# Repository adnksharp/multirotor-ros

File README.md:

# Multirotor-ROS

|  |
|---|

Plataforma de adquisición de datos de un multirotor con ESP32 y ROS2

## Software y Hardware 

<details>
    <summary>Software</summary>

* [ROS2 Jazzy](https://index.ros.org/p/desktop_full/#jazzy)
* [Gazebo Harmonic](https://gazebosim.org/docs/harmonic/getstarted/)
* [uROS Jazzy](https://github.com/micro-ROS/micro_ros_setup/tree/jazzy)
* [uROS Arduino Jazzy](https://github.com/micro-ROS/micro_ros_arduino/tree/jazzy)
* [KiCad](https://www.kicad.org)

</details>

<details>
    <summary>Componentes electrónicos</summary>

* 1 [ESP-WROOM-32 Devkit](https://www.amazon.com/-/es/ESP32-DevKitC-ESP32-WROOM-32-ESP32-WROVER/dp/B07W6F2Z3K)
* 1 Módulo IMU [MPU6050](https://www.amazon.com/-/es/MPU6050-Accelerometer-Gyroscope-Module-Arduino/dp/B00KQK8X2A)
* 1 Módulo GPS [NEO-6M](https://www.amazon.com/-/es/NEO-6M-GPS-Module-For-Arduino/dp/B00KQK8X2A)
* 1 Sensor de temp. y humedad [DHT22](https://www.amazon.com/-/es/DHT11-Temperature-Humidity-Sensor-Arduino/dp/B00KQK8X2A)
* 1 Resistencia de 10KΩ
* 1 Módulo [BMP280](https://www.amazon.com/-/es/BME280-Temperature-Humidity-Barometric-Pressure/dp/B00KQK8X2A)
* 4 Módulos sensores de distancia [HC-SR04](https://www.amazon.com/-/es/HC-SR04-Ultrasonic-Distance-Transducer-Arduino/dp/B00KQK8X2A)
* 1 Pantalla [OLED 0.96"](https://www.amazon.com/-/es/0-96-Inch-OLED-Display-Arduino/dp/B00KQK8X2A)
* 4 Motores brushless [1000KV](https://www.amazon.com/-/es/Brushless-Motor-1000KV-Drone-Quadcopter/dp/B00KQK8X2A)
* 4 Controladores de velocidad [(ESC) 30A](https://www.amazon.com/-/es/Brushless-Controller-30A-Quadcopter-Multicopter/dp/B00KQK8X2A)
* 1 Batería LiPo [2S 4Ah](https://www.amazon.com/-/es/LiPo-Battery-2200mAh-3S-11-1V/dp/B00KQK8X2A)
* 1 Powerbank [30A 3.7V](https://www.amazon.com/-/es/Power-Bank-3-7V-30A/dp/B00KQK8X2A)

</details>

<details>
    <summary>Componentes mecánicos</summary>

* 1 Chasis de multirotor [F450](https://www.amazon.com/-/es/F450-Quadcopter-Frame-Kit-Quadcopter/dp/B00KQK8X2A)
* 4 Hélices [1045](https://www.amazon.com/-/es/1045-Propeller-Quadcopter-Multicopter-Drone/dp/B00KQK8X2A)
* Piezas impresas en 3D

</details>

## Instalación
Es posible instalar el software de [ROS2](https://docs.ros.org/en/jazzy/index.html), [Gazebo](https://gazebosim.org/docs/harmonic/install/) y [micro-ROS](https://micro.ros.org/docs/tutorials/core/overview/) siguiendo los pasos de la documentación oficial o con el script de instalación [install-ros.sh](./src/install-ros.sh):

```shell
$SHELL ./src/install-ros.sh
```

## Espacio de trabajo (ROS2)
[ros-ws](ros-ws) es el espacio de trabajo de ROS2 donde se compila el paquete `fdrone` usando para visualizar y simular el multirotor en Gazebo.

```shell
cd ros-ws
colcon build
```

### Lanzador
El lanzador `display.launch.py` se encarga de visualizar el modelo en RVIZ y Gazebo.

```shell
source install/setup.$(echo $SHELL | awk -F '/' '{print $NF}')
ros2 launch fdrone display.launch.py
```

### Interfaz de usuario
El script `vel_put.py` se desarrolló para enviar velocidades al multirotor desde la terminal enviando valores de tipo `Float64` a tópicos puenteados entre ROS2 y Gazebo.

```shell
source install/setup.$(echo $SHELL | awk -F '/' '{print $NF}')
ros2 run fdrone vel_put.py
```

## Electrónica
[electronic](electronic) contiene el esquema eléctrico de la PCB principal.

|  |  |
|---|---|

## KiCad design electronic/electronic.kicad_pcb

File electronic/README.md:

# Esquema electrónico principal

El proyecto se desarrolló usando [KiCAD](https://www.kicad.org/). [electronic.kicad_pro](electronic.kicad_pro) se desarrollo para comunicar multiples sensores a una placa de ESP32. Los componentes utilizados para esta PCB son:

* 1 **ESP32 WROOM-32** DevKit
* 1 Módulo **MPU6050**
* 1 Módulo **BMP280**
* 1 Módulo **NEO6M GPS**
* 1 Pantalla **OLED 128x64**
* 1 Sensor **DHT22**
* 1 Resistencia de 10K $\Omega$
* 4 Módulos **HC-SR04**
* 1 Conector **B2B-XH-A** para la batería
* 1 Conector **B4B-XH-A** para los motores
* **PinSockets** de 2.54mm

## Esquema

El esquema electrónico se encuentra dividido en 8 partes:

* 5 partes indican los componentes que contienen los módulos **MPU6050**, **BMP280**, **NEO6M GPS**, **OLED 128x64** y **DHT22** y etiquetas de los pines de conexión.
* 1 parte indica la conexión de los módulos **HC-SR04** y etiquetas para los pines de conexión de cada módulo.
* 1 parte indica la conexión de los pines de control de los motores y la lectura del estado de la batería.
* La última parte indica la conexión del ESP32 con los componentes mencionados anteriormente.

## PCB

El diseño de la PCB contiene terminales de tipo PinSocket de 2.54mm para la conexión de los módulos **BMP280**, **NEO6M GPS**, **OLED 128x64**, **HC-SR04** y el **ESP32 WROOM-32**. También contiene un conector de tipo **B2B-XH-A** para la lectura de la batería y un conector de tipo **B4B-XH-A** para el control de los motores. Por último, el diseño de la PCB incluye el módulo **MPU6050**, el sensor **DHT22** y la resistencia de 10K $\Omega$.

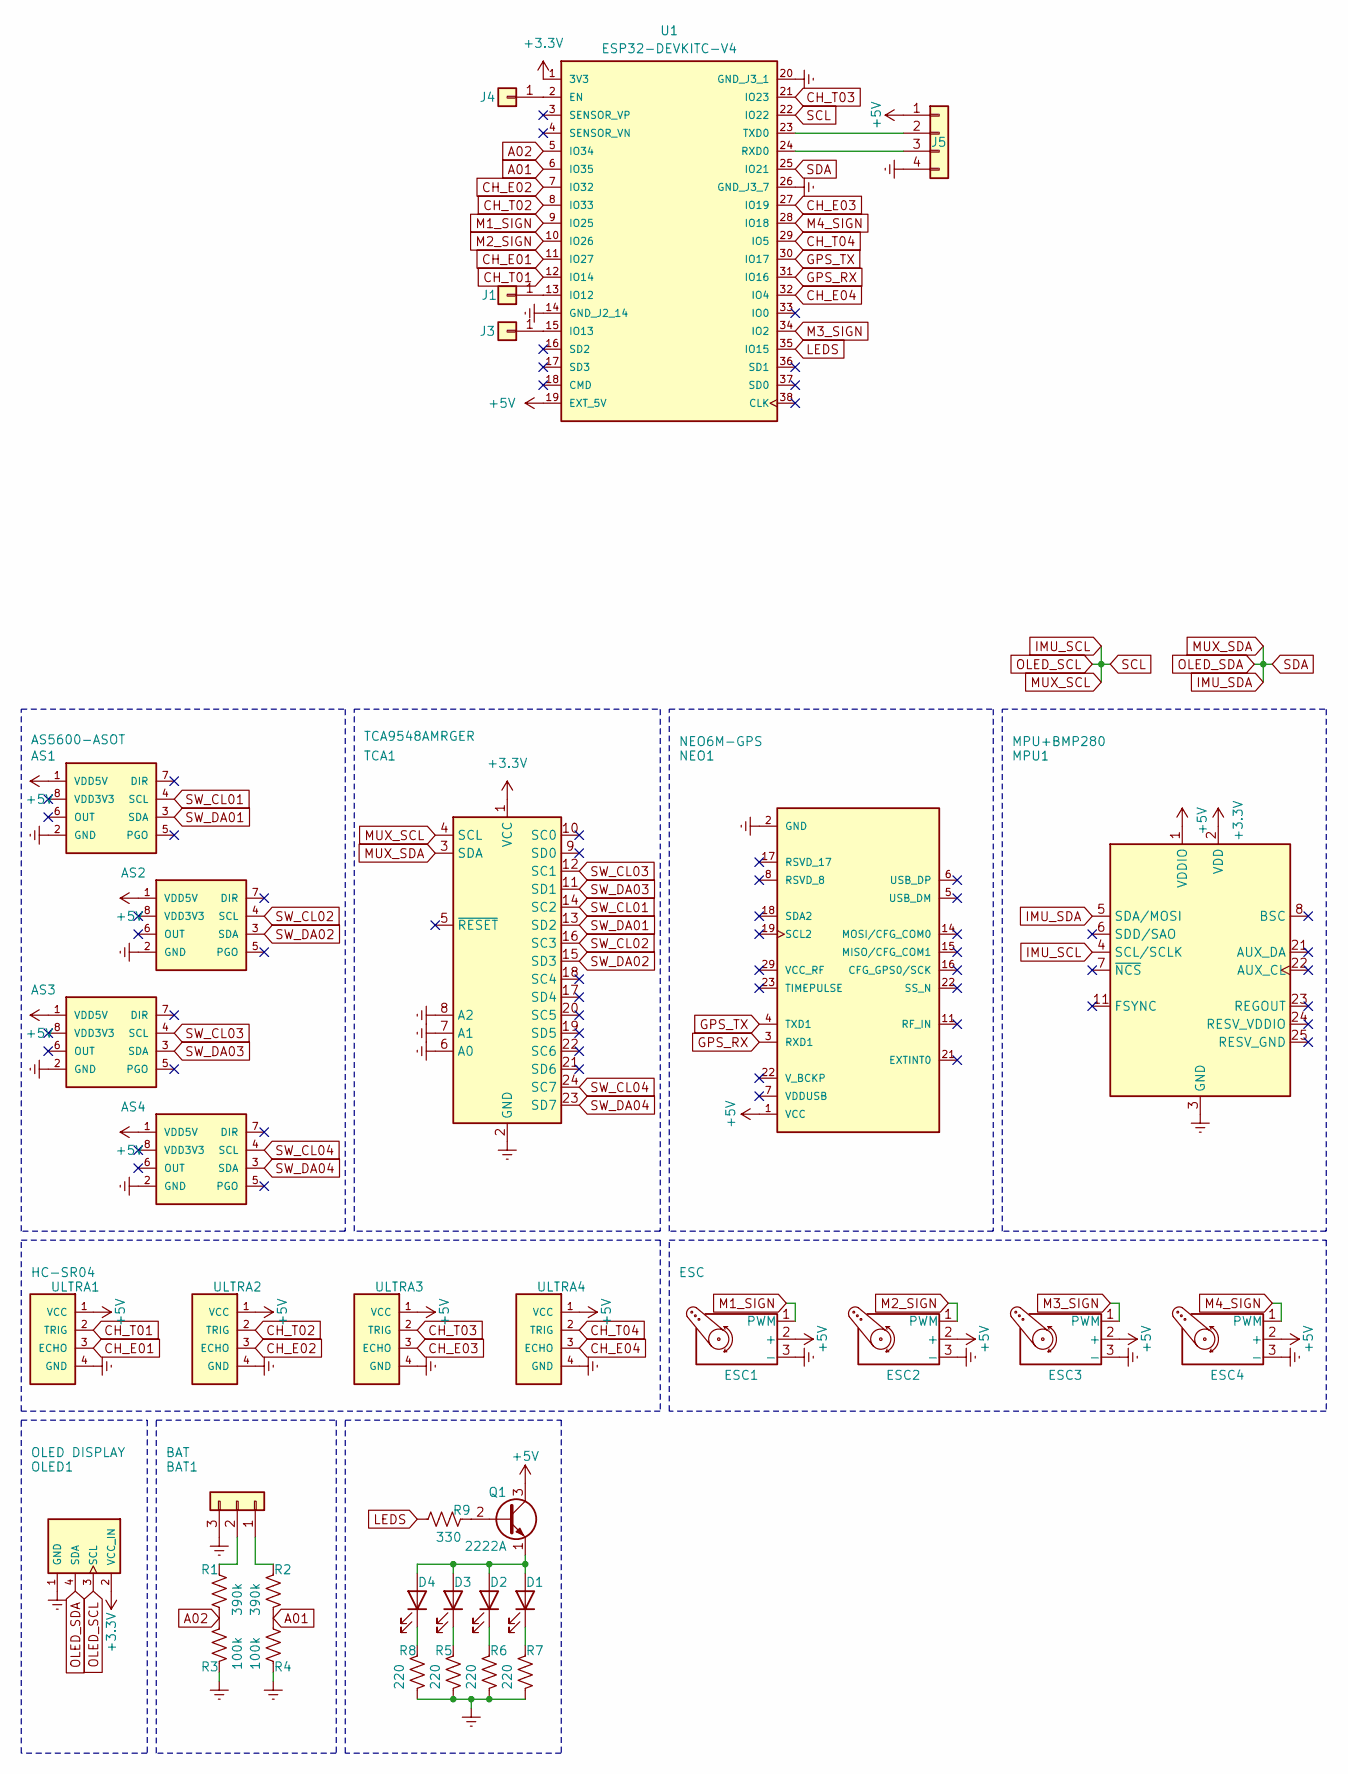
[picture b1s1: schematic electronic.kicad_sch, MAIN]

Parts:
AS1, AS2, AS3, AS4: AS5600-ASOT; PinSocket_1x04_P2.54mm_Horizontal; MOUSER_PART_NUMBER 985-AS5600-ASOT
BAT1: BAT; JST_XH_B3B-XH-A_1x03_P2.50mm_Vertical
D1, D2, D3, D4: LED; PinHeader_1x02_P2.54mm_Vertical
ESC1: ESC; ESC1
ESC2: ESC; ESC2
ESC3: ESC; ESC3
ESC4: ESC; ESC4
J1, J3, J4: Conn_01x01; PinHeader_1x01_P2.54mm_Vertical
J5: Conn_01x02; PinHeader_1x04_P2.54mm_Vertical
MPU1: MPU+BMP280; MPU9250
NEO1: NEO6M-GPS; PinHeader_1x04_P2.54mm_Vertical; PARTREV R15
OLED1: OLED DISPLAY; MODULE_DM-OLED096-636; PARTREV 2018-09-10
Q1: 2222A; TO-92_Inline
R1, R2: 390k; R_0805_2012Metric
R3, R4: 100k; R_0805_2012Metric
R5, R6, R7, R8: 220; R_0805_2012Metric
R9: 330; R_0805_2012Metric
TCA1: TCA9548AMRGER; TCA9548A
U1: ESP32-DEVKITC-V4; MODULE_ESP32-DEVKITC-V4; PARTREV 1.4
ULTRA1, ULTRA2, ULTRA3, ULTRA4: HC-SR04; PinSocket_1x04_P2.54mm_Horizontal

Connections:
+3.3V: MPU1.2 (VDD), OLED1.2 (VCC_IN), TCA1.1 (VCC), U1.1 (3V3)
+5V: AS1.1 (VDD5V), AS2.1 (VDD5V), AS3.1 (VDD5V), AS4.1 (VDD5V), ESC1.2 (+), ESC2.2 (+), ESC3.2 (+), ESC4.2 (+), J5.1, MPU1.1 (VDDIO), NEO1.1 (VCC), Q1.3 (C), U1.19 (EXT_5V), ULTRA1.1 (VCC), ULTRA2.1 (VCC), ULTRA3.1 (VCC), ULTRA4.1 (VCC)
A01: R2.1, R4.1, U1.6 (IO35)
A02: R1.1, R3.1, U1.5 (IO34)
CH_E01: U1.11 (IO27), ULTRA1.3 (ECHO)
CH_E02: U1.7 (IO32), ULTRA2.3 (ECHO)
CH_E03: U1.27 (IO19), ULTRA3.3 (ECHO)
CH_E04: U1.32 (IO4), ULTRA4.3 (ECHO)
CH_T01: U1.12 (IO14), ULTRA1.2 (TRIG)
CH_T02: U1.8 (IO33), ULTRA2.2 (TRIG)
CH_T03: U1.21 (IO23), ULTRA3.2 (TRIG)
CH_T04: U1.29 (IO5), ULTRA4.2 (TRIG)
Earth: AS1.2 (GND), AS2.2 (GND), AS3.2 (GND), AS4.2 (GND), BAT1.3, ESC1.3 (-), ESC2.3 (-), ESC3.3 (-), ESC4.3 (-), J5.4, MPU1.3 (GND), NEO1.2 (GND), NEO1.12 (GND), NEO1.13 (GND), NEO1.24 (GND), OLED1.1 (GND), R3.2, R4.2, R5.1, R6.1, R7.1, R8.1, TCA1.2 (GND), TCA1.6 (A0), TCA1.7 (A1), TCA1.8 (A2), U1.14 (GND_J2_14), U1.20 (GND_J3_1), U1.26 (GND_J3_7), ULTRA1.4 (GND), ULTRA2.4 (GND), ULTRA3.4 (GND), ULTRA4.4 (GND)
GPS_RX: NEO1.3 (RXD1), U1.31 (IO16)
GPS_TX: NEO1.4 (TXD1), U1.30 (IO17)
IMU_SCL: MPU1.4 (SCL/SCLK), OLED1.3 (SCL), TCA1.4 (SCL), U1.22 (IO22)
IMU_SDA: MPU1.5 (SDA/MOSI), OLED1.4 (SDA), TCA1.3 (SDA), U1.25 (IO21)
LEDS: R9.1, U1.35 (IO15)
M1_SIGN: ESC1.1 (PWM), U1.9 (IO25)
M2_SIGN: ESC2.1 (PWM), U1.10 (IO26)
M3_SIGN: ESC3.1 (PWM), U1.34 (IO2)
M4_SIGN: ESC4.1 (PWM), U1.28 (IO18)
unnamed: BAT1.1, R2.2
unnamed: BAT1.2, R1.2
unnamed: D1.2 (A), D2.2 (A), D3.2 (A), D4.2 (A), Q1.1 (E)
unnamed: D1.1 (K), R7.2
unnamed: D2.1 (K), R6.2
unnamed: D3.1 (K), R5.2
unnamed: D4.1 (K), R8.2
unnamed: J1.1 (Pin_1_1), U1.13 (IO12)
unnamed: J3.1 (Pin_1_1), U1.15 (IO13)
unnamed: J4.1 (Pin_1_1), U1.2 (EN)
unnamed: J5.2, U1.23 (TXD0)
unnamed: J5.3, U1.24 (RXD0)
unnamed: Q1.2 (B), R9.2
SW_CL01: AS1.4 (SCL), TCA1.14 (SC2)
SW_CL02: AS2.4 (SCL), TCA1.16 (SC3)
SW_CL03: AS3.4 (SCL), TCA1.12 (SC1)
SW_CL04: AS4.4 (SCL), TCA1.24 (SC7)
SW_DA01: AS1.3 (SDA), TCA1.13 (SD2)
SW_DA02: AS2.3 (SDA), TCA1.15 (SD3)
SW_DA03: AS3.3 (SDA), TCA1.11 (SD1)
SW_DA04: AS4.3 (SDA), TCA1.23 (SD7)

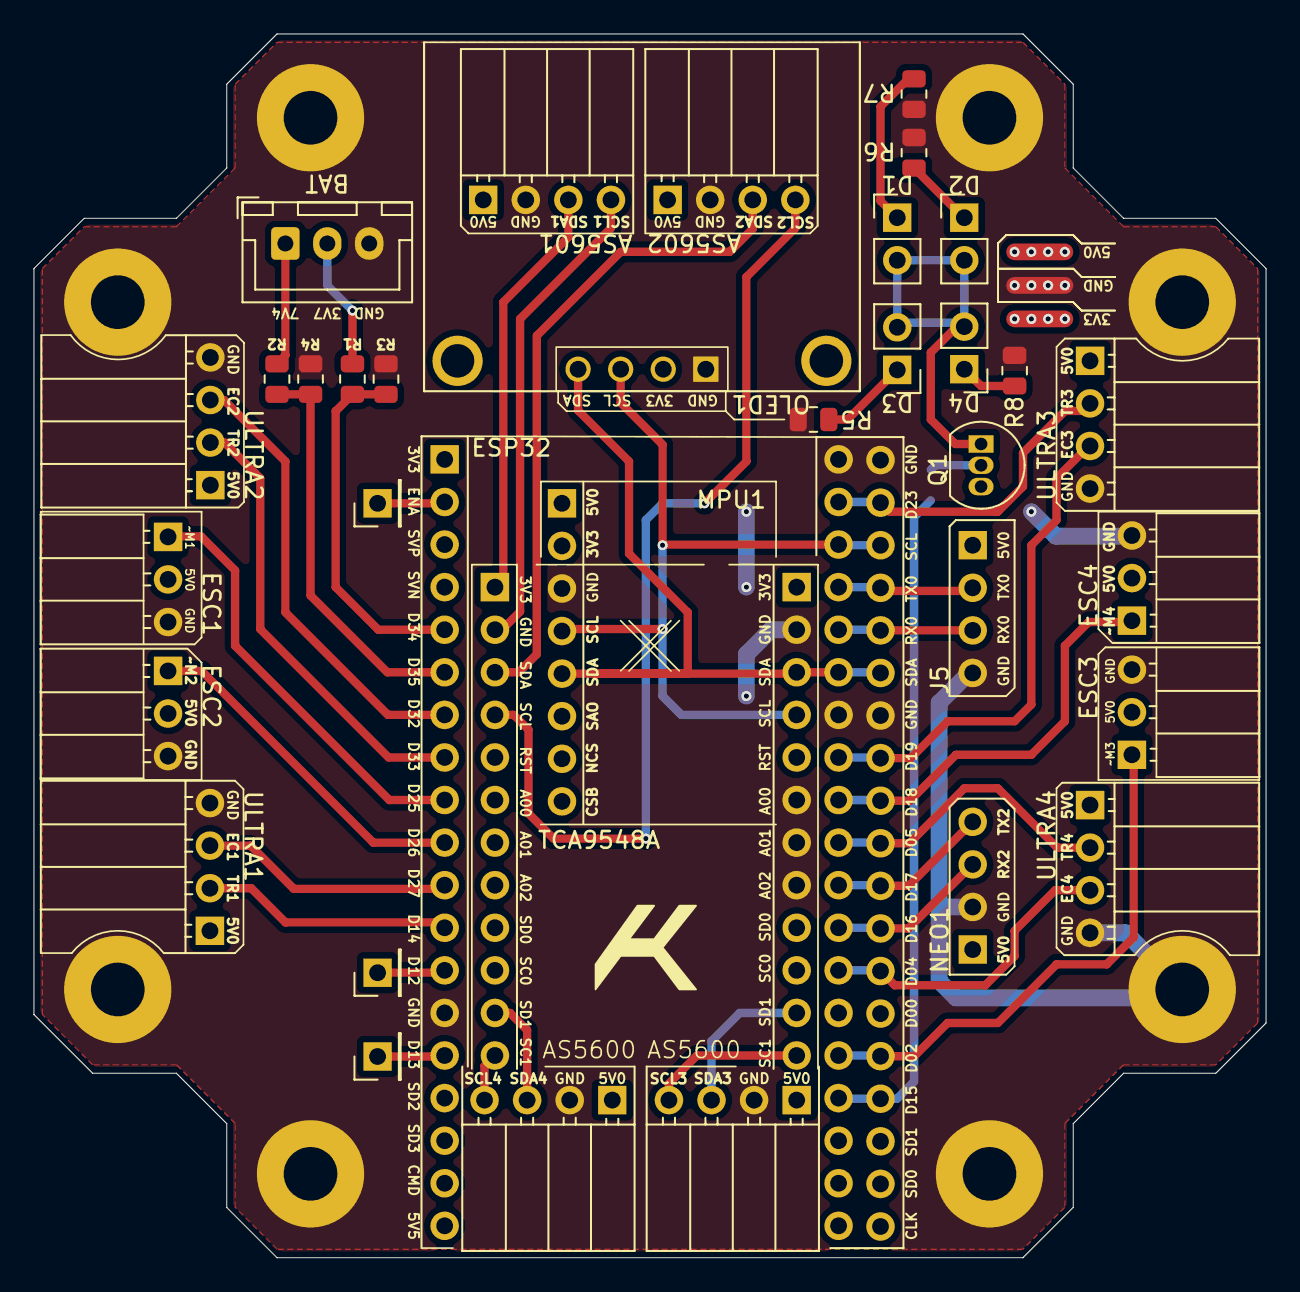
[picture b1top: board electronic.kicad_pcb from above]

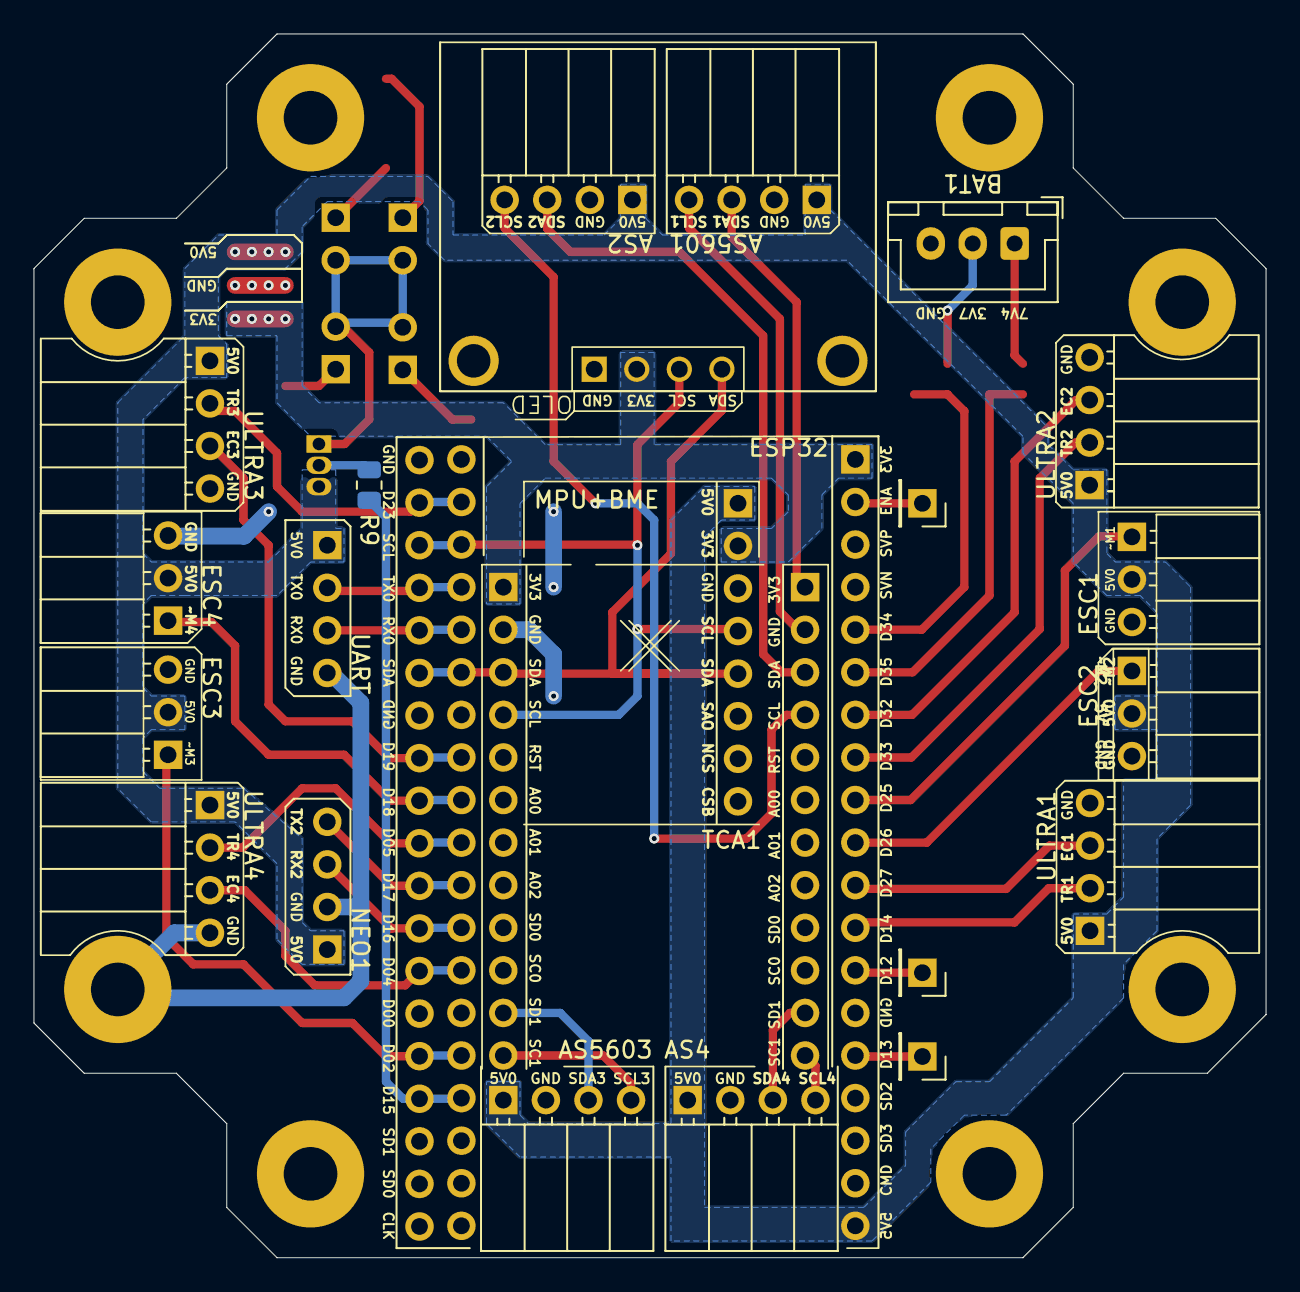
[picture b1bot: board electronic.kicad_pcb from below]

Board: 2 copper layers, 73.5 x 73.0 mm, 36 parts (10 on the bottom side), 43 nets.

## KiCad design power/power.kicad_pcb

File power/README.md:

# Esquema electrónico secundario

El proyecto  [power.kicad_pro](power.kicad_pro) se desarrolló para conectar controladores ESC con motores brushless a un microcontrolador ESP32. Los componentes utilizados para esta PCB son:

* 2 resistencias de 10K $\Omega$.
* 2 resistencias de 4.7K $\Omega$.
* 1 conector de tipo **B2B-XH-A**.
* 2 conectores de tipo **B3B-XH-A**.
* 1 conector de tipo **B5B-XH-A**.
* 4 conectores de tipo **PinHeader 1x03** de 2.54mm.
* 5 teriminales para soldar cable 1x02 de 2.4mm.

## Esquema

El esquema electrónico se encuentra dividido en 11 partes:

* 4 partes corresponden a los controladores ESC y sus etiquetas para conectar los motores brushless, la señal de control y la alimentación.
* 4 partes corresponden a los motorres brushless y sus etiquetas para conectar los controladores ESC.
* 1 parte corresponde a la conexión de una batería de 2S a los controladores ESC.
* 1 parte corresponde a la conexión del cargador de batería.
* La última parte corresponde a la conexión del microcontrolador ESP32.

## PCB

Se diseño la PCB para conectar la alimentación de los controladores ESC con la batería de 2S usando las terminales de soldadura. Los conectores PinHeader se utilizan para conectar las señales de control de los ESC y el conector B5B-XH-A se utiliza para conectar el microcontrolador ESP32 a estos pines. El conector B2B-XH-A se utiliza para leer el estado de la batería mediante divisores de voltaje hechos con resistencias de 10K $\Omega$ y 4.7K $\Omega$. El conector B3B-XH-A se utiliza para conectar el cargador de batería a la PCB.

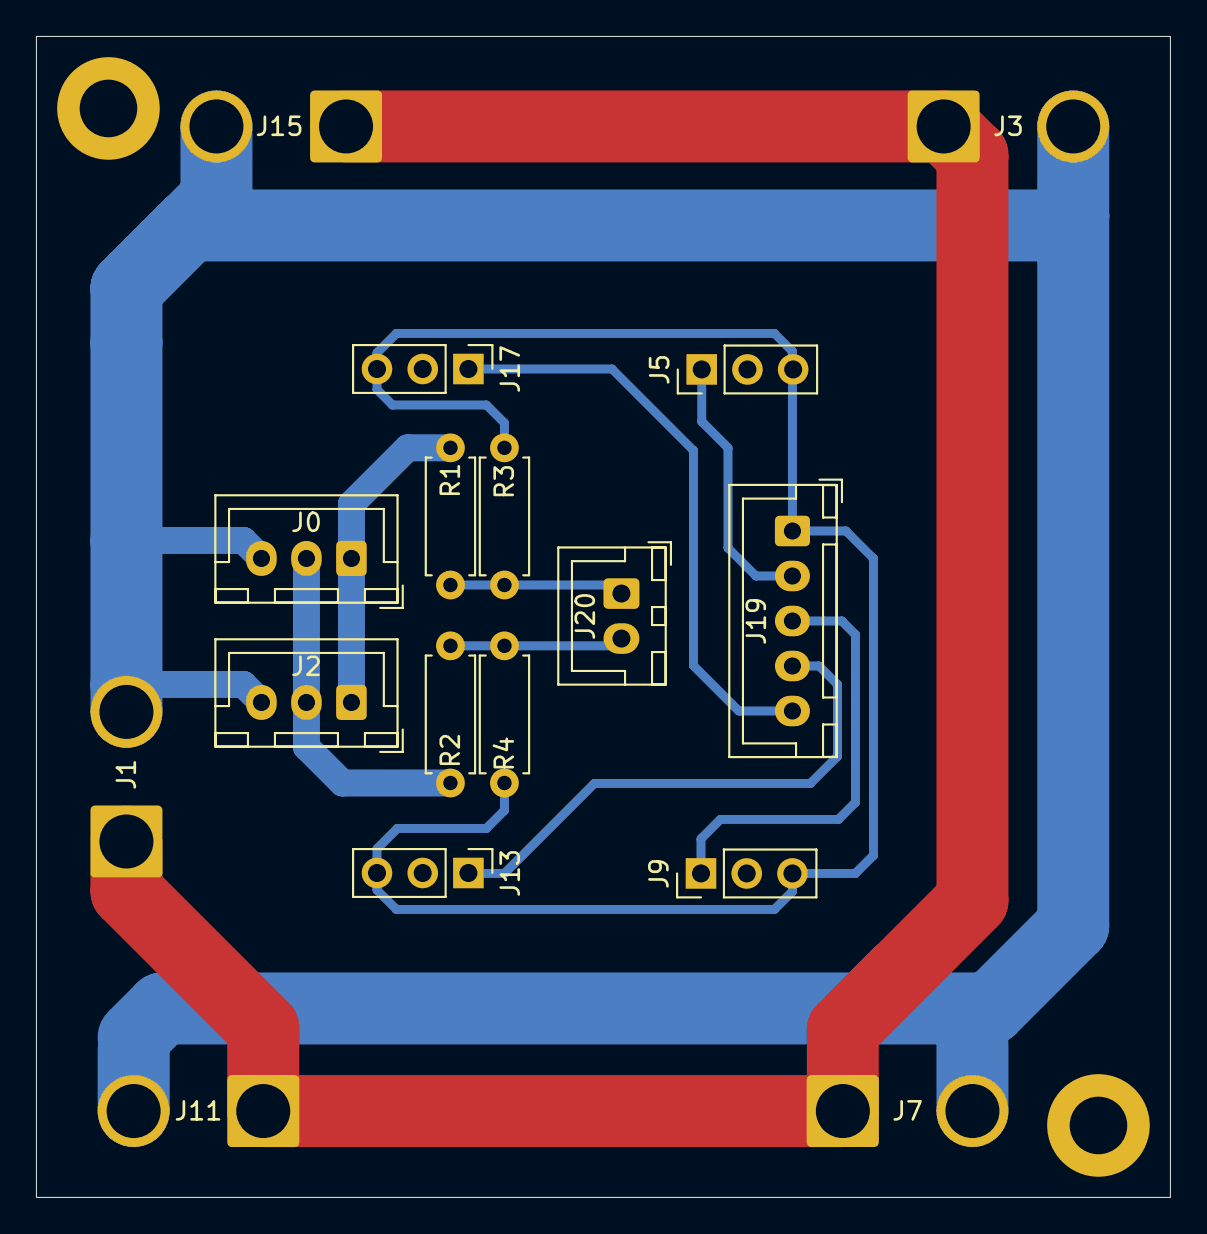
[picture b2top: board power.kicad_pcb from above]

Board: 2 copper layers, 63.0 x 64.5 mm, 17 parts (0 on the bottom side), 11 nets.

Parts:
J0, J2: JST-XH conn; JST_XH_B3B-XH-A_1x03_P2.50mm_Vertical
J1, J3, J7, J11, J15: BAT-conn; SolderWire-2.5sqmm_1x02_P7.2mm_D2.4mm_OD3.6mm
J5, J9, J13, J17: PWM Conn; PinHeader_1x03_P2.54mm_Vertical
J19: ESP_OUT; JST_XH_B5B-XH-A_1x05_P2.50mm_Vertical
J20: ESP_IN; JST_XH_B2B-XH-A_1x02_P2.50mm_Vertical
R1, R2: 10k; R_Axial_DIN0207_L6.3mm_D2.5mm_P7.62mm_Horizontal
R3, R4: 4.7k; R_Axial_DIN0207_L6.3mm_D2.5mm_P7.62mm_Horizontal

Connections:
+BATT: J1.1, J3.1, J7.1, J11.1, J15.1
-BATT: J0.3, J1.2, J2.3, J3.2, J7.2, J11.2, J15.2
A01: J0.2, J2.2, R2.1
A02: J0.1, J2.1, R1.1
D_01: J5.1, J19.2
D_02: J9.1, J19.3
D_03: J13.1, J19.4
D_04: J17.1, J19.5
Earth: J5.3, J9.3, J13.3, J17.3, J19.1, R3.1, R4.1
unnamed: J20.1, R1.2, R3.2
unnamed: J20.2, R2.2, R4.2

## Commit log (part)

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2025-03-03 chore: python ignored added
2025-03-03 chore: ros workspace init
2025-03-03 test: ESP32 ROS2-jazzy publisher tested
2025-03-03 test: ESP32 ROS2-jazzy publisher tested with wifi
2025-03-04 test: echo-talker of ESP32 using uROS
2025-03-05 chore: mpu6050 added, reading temp
2025-03-05 chore: publishing gyro and accelertion status of mpu
2025-03-05 ops: esp32 node changed
2025-03-07 docs: update README.md
2025-03-08 test: Read driver topics with listener.py, ESP32 BEST EFFORT QoS publishers changed to RELIABLE
2025-03-08 test: Read driver topics with listener.py in a dict
2025-03-09 docs: README updated
2025-03-11 chore: KICAD files init
2025-03-11 dos: update README.md
2025-03-11 feat: motors, DHT11 and BMP280 added to electronic schematic
2025-03-12 feat: MPU6050, NEO-6M and OLED display added to electronic schematic
2025-03-13 chore: .gitignore updated
2025-03-15 chore: ESP32 devkit changed of schematic
2025-03-15 chore: PCB design added to the project
2025-03-22 refactor (electronic): update PCB design
2025-03-22 feat(urdf-ws): make URDF files with sw2urdf
2025-03-24 refactor (electronic, power): separate the project PCB in two
2025-03-24 chore (.gitignore): update excluded files
2025-03-24 refactor(URDF.SLDASM): move generated sw2urdf
2025-03-24 feat(ros-ws): start urdf project, publish robot with ROS2 and gazebo
2025-03-24 docs (README.md): add gz instructions
2025-03-28 chore(fdrone): rename *_*.STL files to *.STL and add launcher for display the project in rviz2
2025-03-31 feat(fdrone): control velocities in rviz2
2025-03-31 feat(ros-ws/main): update main package from ament_python to ament_cmake
2025-04-06 refactor (model.urdf): test gz-sim-multicopter-control-system plugin
2025-04-06 refactor (img): update images
2025-04-07 chore(ros-ws): test control of joints with gz-sim-joint-controller-system
2025-04-07 fix(model.urdf): set test limit effort for joints
2025-04-08 refactor(ros-ws): change names of topics, nodes and elements in the urdf
2025-04-08 refactor(ros-ws): update joint states for visualize the model in RViz with gazebo data
2025-04-09 refactor(ros-ws): change pos_pub.py to get_pub.py
2025-04-09 refactor(ros-ws): change pos_pub.py to pos_get.py
2025-04-09 refactor(ros-ws): change vel_pub.py to vel_put.py
2025-04-11 refactor(ros-ws): change the filename attrib in urdf to use relative directory based on the project
2025-04-18 chore (electronic | power): update electronic subprojects
2025-04-18 feat(install-ros.sh): add script for automate installation
2025-04-19 chore(electronic): add NEO 6M step file
2025-04-20 chore(ros-ws): update UAV base
2025-04-20 docs (README.md): update markdown files
2025-05-03 test (yamanaka): test hardware with arduino
2025-12-05 refactor (electronic): Init migrate kicad libraries
2025-12-08 refactor (electronic): Add local AS5600 module library for KiCad
2025-12-08 refactor (electronic): Add local HC-SR04 module library for KiCad
2025-12-08 refactor (electronic): Add local NEO-6M module library for KiCad
2025-12-08 refactor (electronic): Add local OLED Display module library for KiCad
2025-12-08 refactor (electronic): Add local TCA Multiplexer module library for KiCad
2025-12-08 refactor (electronic): Add local MPU9250 modified library for KiCad
2025-12-08 refactor (electronic): Add local ESP32 Devkit V4 library for KiCad
2025-12-08 refactor (electronic): Add local custom footprints for KiCad
2025-12-08 feat (electronic): Unify electronic and power PCBs into one
2025-12-08 docs (electronic): Update 3D PCB preview
2025-12-08 docs (electronic): Update markdown files
2025-12-08 refactor (electronic): update PCB tabs for PCBWay
2025-12-08 refactor (img): update pictures
